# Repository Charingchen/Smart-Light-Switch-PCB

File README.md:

# Smart Light Switch PCB
This board is powered by Flyback converter, converting 120VAC to 5VDC to power the ESP32 microcontroller. The onboard temperture sensor and montion sensor would be used for smart home configrations 
## Flyback Converter Schematic

## PCB

## Rev 1 Flyback Assemble PCB

## Kicad
This project uses Kicad to draw schematic and PCB
You can download [Kicad](https://kicad.org/) and open SLS_rev1.pro

### Digikey Library
I used digikey kicad Library to place most of the components:
https://www.digikey.ca/en/resources/design-tools/kicad

## Blog Post

I wrote some blog post talk about flyback controller, you can check them out below:

 <a target="_blank" href="https://github-readme-medium-recent-article.vercel.app/medium/@charingchen/2">
 
 <a target="_blank" href="https://github-readme-medium-recent-article.vercel.app/medium/@charingchen/3">

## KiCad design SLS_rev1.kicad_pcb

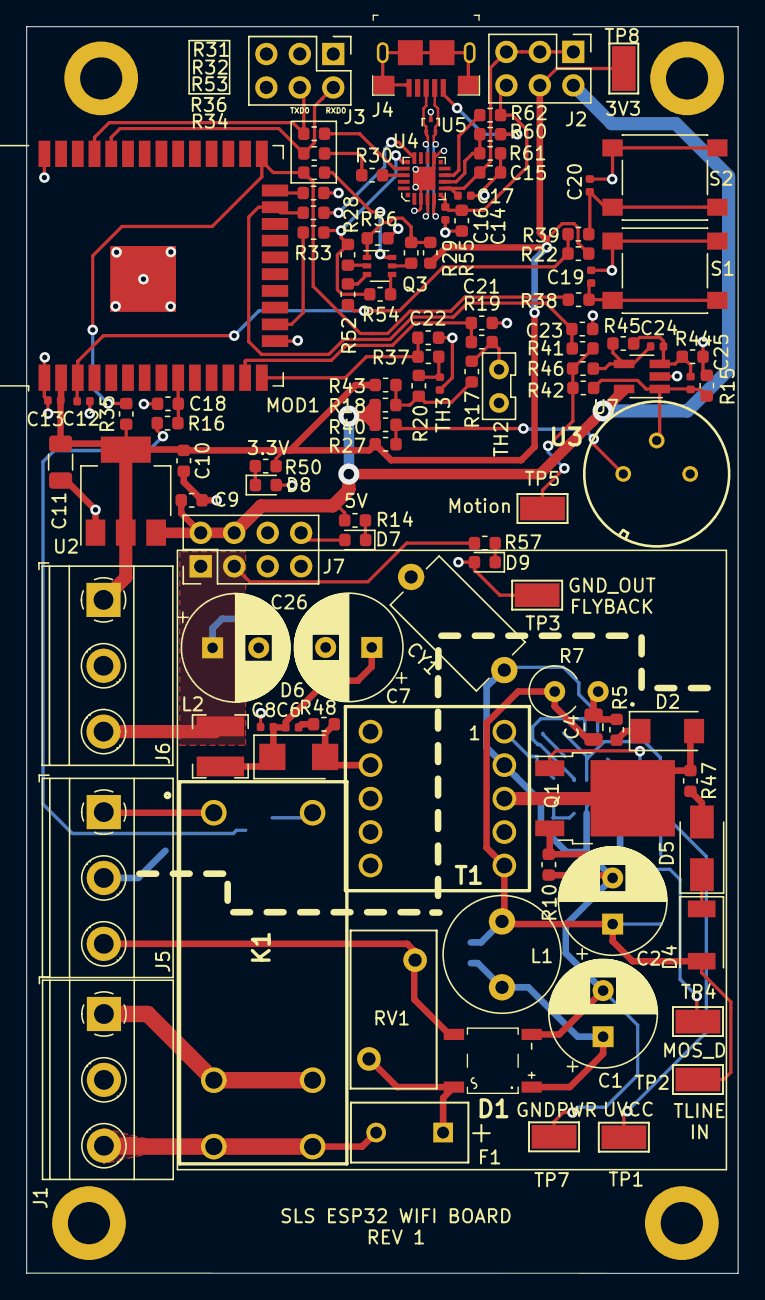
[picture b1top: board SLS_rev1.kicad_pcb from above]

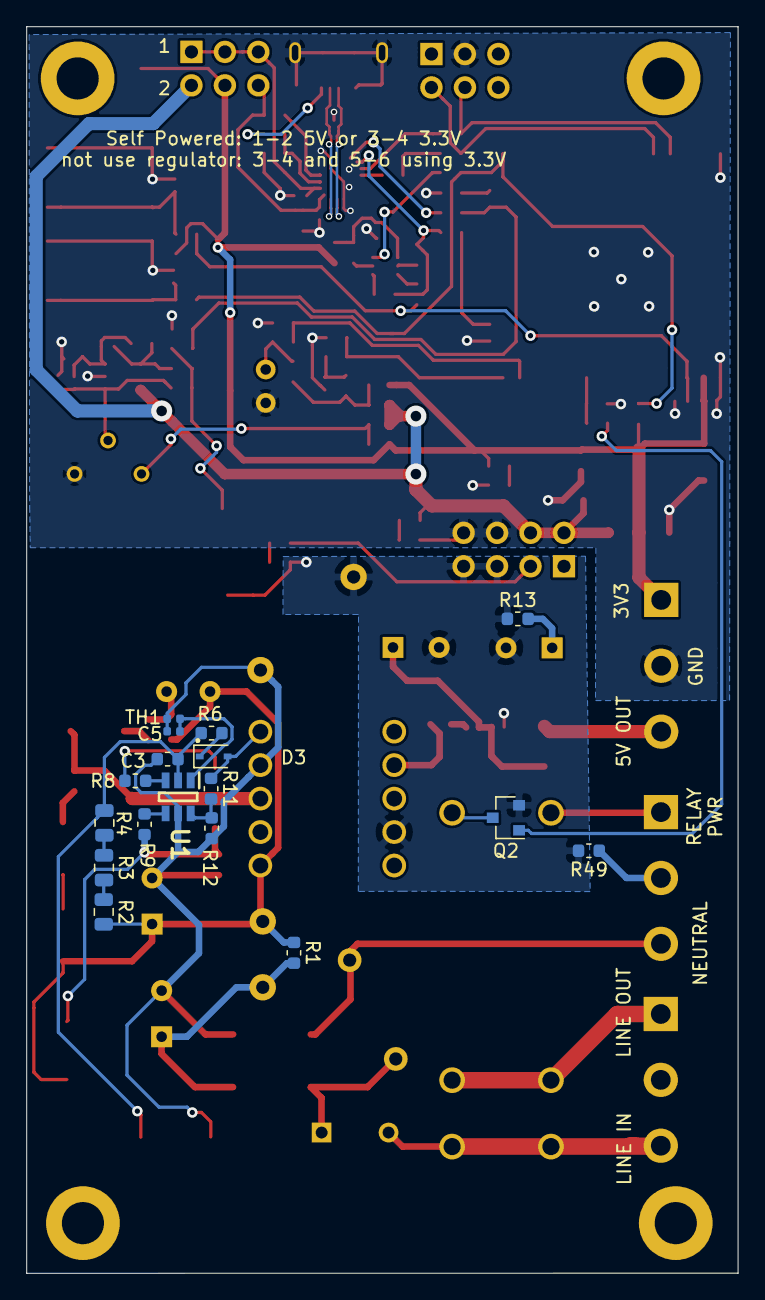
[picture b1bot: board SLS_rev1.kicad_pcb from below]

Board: 2 copper layers, 54.0 x 94.6 mm, 129 parts (17 on the bottom side), 76 nets.

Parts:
C1: 6.8uF; CP_Radial_D8.0mm_P3.50mm
C2: 10uF; CP_Radial_D8.0mm_P3.50mm
C3: 10uF 25V; C_0603_1608Metric
C4: 22nF 250V; R_0805_2012Metric
C5, C24, C25: 15pF; R_0402_1005Metric
C6: 2200pF; C_0402_1005Metric
C7, C26: 820uF; CP_Radial_D8.0mm_P3.50mm
C8, C12, C13: 1uF; C_0402_1005Metric
C9, C10, C14, C15, C18, C21, C22, C23: 4.7uF; R_0603_1608Metric
C11: 100uF 6.3V; C_1206_3216Metric
C16, C17: 0.1uF; C_0402_1005Metric
C19, C20: 1nF; C_0402_1005Metric
CY1: 100pF 440VAC; C_Disc_D9.0mm_W5.0mm_P10.00mm
D1: MDB6S
D2: 1.2V @1A; D_GF1
D3: 200V 200mA SOD323; D_SOD-323
D4: SMAJ90A
D5: MRA4007T3G; D_SMA
D6: NRVTSA4100E; D_SMA
D7, D8, D9: LTST-C190KGKT; LED_0603_1608Metric
F1: 0697H1000-02
H1, H2, H3, H4: MountingHole; MountingHole_3.2mm_M3_DIN965_Pad
J1, J5, J6: Phoenix_3pos_5mm; TerminalBlock_Phoenix_MKDS-1,5-3_1x03_P5.00mm_Horizontal
J2, J3: Conn_02x03_Odd_Even; PinHeader_2x03_P2.54mm_Vertical
J4: 10118193-0001LF; USB_Micro_B_Female_10118193-0001LF
J7: Conn_02x04_Odd_Even; PinHeader_2x04_P2.54mm_Vertical
K1: RZ03-1A4-D005
L1: 220uH; L_Radial_D8.7mm_P5.00mm_Fastron_07HCP
L2: 1uH; L_Bourns-SRN4018
MOD1: ESP32-WROOM-32
Q1: SIHD2N80E; TO-252-2
Q2: SSM3K257R; SOT-23
Q3: MBT3904DW1T1G; SOT-363_SC-70-6
R1, R13, R44, R49, R62: 1k; R_0603_1608Metric
R2, R3, R4: 590k; R_0805_2012Metric
R5, R47: 51.1; R_0603_1608Metric
R6, R48: 21.5; R_0603_1608Metric
R7: 220k; R_Axial_DIN0309_L9.0mm_D3.9mm_P2.54mm_Vertical
R8: 10; R_0603_1608Metric
R9: 374; R_0603_1608Metric
R10: 1.02; R_0603_1608Metric
R11: 90.9k; R_0603_1608Metric
R12: 24.9k; R_0603_1608Metric
R14, R50, R57: 2k; R_0603_1608Metric
R15: 43k; R_0603_1608Metric
R16, R18, R19, R27, R31, R32, R33, R34, R37, R40, R41, R42, R43, R46, R52, R53, R54, R55, R56: R_0ohm; R_0603_1608Metric
R17, R28, R29, R35, R36: 10k; R_0603_1608Metric
R20: 100k; R_0603_1608Metric
R22: 12k; R_0603_1608Metric
R30, R38, R39: 470; C_0603_1608Metric
R45: 75k; R_0603_1608Metric
R60: 22.1K; R_0603_1608Metric
R61: 47K; R_0603_1608Metric
RV1: 510V; ERZ10D511
S1, S2: PTS645SM43SMTR92_LFS; SW_SPST_PTS645
T1: Transformer_120V_PRI_15V_AUX; 7508110151
TH1: X_NTC 470K; R_0402_1005Metric
TH2: 10k NTC; NTCLE100E3103ht1
TH3: 100k NTC; R_0402_1005Metric
TP1, TP2, TP3, TP4, TP5, TP7, TP8: Keystone5015; TestPoint_Keystone_5015_Micro-Minature
U1: UCC28704; UCC28704DBVR-1
U2: AP2114H-3_3TRG1; SOT-223-3_TabPin2
U3: IRA-S210ST01; VZ-STANDARD
U4: CP2102N-A02-GQFN20R; QFN-20-1EP_3x3mm
U5: TPD2EUSB30; Texas_DRT-3
U7: LMV321; SOT-23-5_HandSoldering

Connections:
+3V3: C10.1, C11.1, C13.1, J2.4, J6.1, MOD1.2, R22.1, R27.1, R35.1, R43.1, R50.1, R55.1, TP8.1, U2.2
+5V: C9.1, J2.2, J7.2, J7.4, R14.1, R18.1, R40.1, U2.3, U7.5
/Flyback/5V_OUT: C26.1, J6.3, J7.1, J7.3, L2.2, R13.2, R57.2
/Flyback/GATE: Q1.1, R8.1
/Flyback/GND_OUT: C7.2, C8.2, C26.2, CY1.2, D9.2, J7.5, J7.7, Q2.2, R13.1, R49.2, T1.7, TP3.1
/Flyback/MOS_D: Q1.3, R9.1, R10.2, TP4.1
/Flyback/T_AUX: D3.2, R11.2, T1.1
/Flyback/T_LINE_IN: C2.1, C4.1, D4.2, L1.2, R1.1, R2.2, R7.1, T1.5, TP2.1
/Flyback/T_LINE_OUT: D2.A, Q1.2, R47.1, T1.3
/Flyback/U_VCC: C3.1, R4.1, R6.2, TP1.1, U1.2
/Flyback/VS: R11.1, R12.2, U1.6
/LINE_IN: F1.2, J1.3, K1.3, K1.4
/LINE_OUT: J1.1, K1.2, K1.5
/NEUTRAL: D1.3, J5.3, RV1.2
/Relay_switch/CONTROL: Q2.1, R16.2
/Relay_switch/VCC: J5.1, K1.1
/esp32 controlller/ADC1_CH0: C21.2, MOD1.13, R19.1
/esp32 controlller/ADC1_CH3: C22.2, MOD1.14, R37.1
/esp32 controlller/ADC1_CH6: C23.2, MOD1.23, R34.1, R41.1
/esp32 controlller/CTS: R34.2, U4.15
/esp32 controlller/DTR: Q3.1, R29.2, R55.2, R56.1
/esp32 controlller/EN: C12.1, MOD1.3, R22.2, R39.1, R52.2
/esp32 controlller/IO0: MOD1.25, R35.2, R38.1, R53.1
/esp32 controlller/IO2: MOD1.24, R36.1
/esp32 controlller/IO13: MOD1.16, R33.1
/esp32 controlller/IO33: C18.2, MOD1.9, R16.1
/esp32 controlller/MONTION_IN: R41.2, R42.2, R46.1, TP5.1
/esp32 controlller/RTS: R28.1, R33.2, R54.1, U4.16
/esp32 controlller/RXD: R31.2, U4.17
/esp32 controlller/RXD0: J3.2, MOD1.34, R32.1
/esp32 controlller/TEMP_IN_1: R17.2, R19.2, TH2.1
/esp32 controlller/TEMP_IN_2: R20.2, R37.2, TH3.1
/esp32 controlller/TXD: R30.1, R32.2
/esp32 controlller/TXD0: J3.4, MOD1.35, R31.1
/esp32 controlller/USB_D+: J4.3, U4.4, U5.1
/esp32 controlller/USB_D-: J4.2, U4.5, U5.2
/esp32 controlller/USB_VBUS: J4.1, R60.2
/esp32 controlller/USB_VDD: C14.2, C16.2, J2.6, R62.1, U4.6
/esp32 controlller/USB_VREGIN: C15.2, C17.2, J2.1, J2.3, J2.5, U4.7
Earth: J5.2, R49.1
GND: C9.2, C10.2, C11.2, C12.2, C13.2, C14.1, C15.1, C16.1, C17.1, C18.1, C19.2, C20.2, C21.1, C22.1, C23.1, D7.2, D8.2, J3.3, J4.5, J4.SH, J6.2, J7.6, J7.8, MOD1.1, MOD1.15, MOD1.38, MOD1.39, R15.2, R36.2, R44.2, R56.2, R61.2, S1.1, S1.2, S2.1, S2.2, TH2.2, TH3.2, U2.1, U3.3, U4.3, U4.12, U4.21, U5.3, U7.2
GNDPWR: C1.2, C2.2, C3.2, C5.2, CY1.1, D1.2, R10.1, R12.1, T1.2, TH1.2, TP7.1, U1.5
unnamed: C1.1, D1.1, L1.1, R1.2
unnamed: C4.2, R5.2, R7.2
unnamed: C5.1, TH1.1, U1.1
unnamed: C6.1, C7.1, C8.1, D6.1, L2.1
unnamed: C6.2, R48.1
unnamed: C19.1, R38.2, S1.3, S1.4
unnamed: C20.1, R39.2, S2.3, S2.4
unnamed: C24.1, R45.1, R46.2, U7.4
unnamed: C24.2, C25.2, R44.1, R45.2, U7.3
unnamed: C25.1, R15.1, R42.1, U3.2, U7.1
unnamed: D1.4, F1.1, RV1.1
unnamed: D2.K, R5.1
unnamed: D3.1, R6.1
unnamed: D4.1, D5.1
unnamed: D5.2, R47.2
unnamed: D6.2, R48.2, T1.9
unnamed: D7.1, R14.2
unnamed: D8.1, R50.2
unnamed: D9.1, R57.1
unnamed: K1.6, Q2.3
unnamed: Q3.2, R28.2
unnamed: Q3.3, R52.1
unnamed: Q3.4, R54.2
unnamed: Q3.5, R29.1
unnamed: Q3.6, R53.2
unnamed: R2.1, R3.2
unnamed: R3.1, R4.2
unnamed: R8.2, U1.3
unnamed: R9.2, U1.4
unnamed: R17.1, R18.2, R20.1, R43.2
unnamed: R27.2, R40.2, U3.1
unnamed: R30.2, U4.18
unnamed: R60.1, R61.1, U4.8
unnamed: R62.2, U4.9

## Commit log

2020-11-25 doc: add sch and pcb images for readme
2020-11-25 doc: add images to readme
2020-11-25 doc: add pictures and articles links in the readme
2020-12-07 Update Medium article links
2021-02-02 doc: update blog post links

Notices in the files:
parts and their libraries:
Copyright 2016 Accelerated Designs. All rights reserved.
